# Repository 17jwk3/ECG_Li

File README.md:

# Real-time Wearable-based Cardiac Monitoring with Machine Learning
This project was part of ELEC490/498: Electrical Computer Engineering Capstone Project. A 3 semester long undertaking at Queen's Univeristy, Ontario, Canada. 

## Design Problem
Heart disease describes a range of conditions that affect a person’s heart, including blood vessel disease, arrhythmias, valve disease, etc.Various tests are used to diagnose heart conditions. Doctors start with a risk assessment looking into medical history, blood pressure, as well as past and current symptoms but further tests may be required. These methods can be hard to access for most people, due to socio-economic factors. This is a long and outdated process in the digital era of telemedicine. Doctors and patients need fast, easily accessible procedures. 

Many forms of it can be prevented with healthy lifestyle choices and medical interventions. Stress can affect the body mentally and physically left unchecked manifests as an increased heart rate among other symptoms contributing to high blood pressure, diabetes, and heart disease.

Computational advancements have increased the ability to concurrently predict and prevent cardiac abnormalities. Thus creating faster, less intrusive, and more easily accessible methods for patients and practitioners alike.

## Design and Implementaiton

Low-cost ECG (electrocardiogram) electrodes using a 3 lead configuraiton are used to capture impulses through the heart muscles and transmit the information via Bluetooth to a machine-learning algorithm in real-time to provide actionable feedback on potential abnormalities and stress levels via a Graphical User Interface, as seen in the following implementation pipeline.

---------------

### Hardware @17jwk3

The PCB uses a ESP32-C3-MINI-1-N4, a Li-Po with a battery charging module and a buck conmverter to supply 3.3V to the rest of the components. 
The main ECG components are an AD8232 opAmp board utilized for reading the electrical signals of the wearers heart and jack port for the 3 leads. 

#### PCB
This is a 4 layer PCB board that uses a AD8232 breakout board for the ECG pickup. 
The schematic, featuring over charge and discharge protection, switches to control: MCU power, 5V (charging) and Battery power. Also includes ESD protection for usb type C. The brains is an ESP32-C3-MINI-1-N4.

#### PCB layout 

#### Schematic

#### Findings & Changes

The selected ESP32 module was a "standard" component for JLCPCB which means it costed much more to manufacture this board then originally anticipated. A chip that does not require "standard" assembly would be selected going forward. 

With more time, the AD8232 module would be integrated onto the board to increase portability with a very small lipo battery. Additional changes would be made to optimize the layout, add more LEDs for feedback etc. 

The output of the AD8232 may have needed to include a pulldown resistor. 

---------------

### Data Acquisition @17jwk3
#### Design
Data is acquired using the AD8323 amplifier and processed by the ESP32 microcontroller. The amplifier is connected to a 3-lead system placed on the end-user’s person. The top L and R leads are used for data acquisition, while the third and lower lead is the grounding lead.  

The data is sampled at 6 seconds with a 115,200 baud rate. It uses a fixed 360 frequency in accordance with the arrhythmia dataset. Heart beats are characterized by shape and frequency. Abnormalities distinguished by pace (Sinus Arrhythmia, Bradycardia, etc.) would incur informational loss or distortion from domain resampling .

The firmware was coded using the Arduino IDE, a variant of the C++ programming language. It records when both L and R leads sense an electrical signal, as to avoid null readings from not being applied.

In order to create the dataset locally, run 'Models and Prediction/reciever.py'.

#### Findings & Changes

Modification in limb electrode placement invokes changes in ECG wave amplitudes, which may alter the clinical limits of ECG normality detection. It was uncovered that leads placed no further than 12” apart yield the cleanest readings. 

---------------

### Processing and Filtering @CTy27
#### Design
Processing was designed to address missing values and noise artifacts from the raw ECG data using the appropriate filtering methods.

The constraints surrounding hardware filters far outweighed those using software, as hardware filters are more expensive, more difficult to test, and would increase the PCB footprint. Software filtering allows for greater control and optimization which leads to a more optimally processed resulting signal.

A technique known as imputation was used to recover lost values by synthesizing datapoints that hardware failed to capture. Particularly, K-Nearest Neighbors (KNN) imputation is a method used to impute missing values by finding the K closest observations and using their respective values to ‘fill in’ the missing ones. In the application of ECG processing, this method of imputation is beneficial as it accounts for the temporal structure of the data, making KNN imputation a natural choice.

The chosen implementation uses a 3rd order, lowpass Butterworth filter with a cutoff frequency of 50 Hz. 50Hz was found to be the optimal amount as observable high-frequency artifacts from power line interference and EMG were removed without limiting the low-frequency salient information. Lowering this cut-off frequency further resulted in distortion to the amplitude of the peaks, which would have adversely affected the prediction model’s performance. 

#### Findings & Changes
Testing different filters and parameters was largely trial and error testing. Lowpass, high pass, bandpass, and notch filters were all tested, adjusting cut-off frequencies and passbands as appropriate. 

High pass and bandpass filters were susceptible to baseline wander, from samples 4,000 – 5,000 that the signal baseline drifts upwards. The high pass was also unable to filter out the high-frequency noise induced by Electromyography muscular activity (EMG), motion artifacts, and residual channel noise. The clear choice was lowpass as it maintains the salient, low-frequency information without distorting the signal with baseline wander. 

There lies uncertainty in the exclusive use of lowpass to filter out noise, as a bandpass and a notch filter ensemble are standard for ECG data.  Solely relying on low-pass filters is not a common approach, however, the final product was sufficient for the classification models to perform adequately. 

---------------

### Arrhythmia Detection @alexkoch14
#### Design
The arrhythmia model was trained on the MIT-BIH database, containing 48-half-hour excerpts of two-channel ambulatory ECG recordings, obtained from 47 subjects studied by the BIH arrhythmia laboratory between 1975 and 1979.

The recordings were digitized at 360 samples per second and two or more cardiologists independently annotated each record.

The recordings were extracted using wfdb, the Python wave-form database package. ECG signals are transformed into snippets during the data pre-processing step as the model analyzes one-dimensional input data. 

Heartbeats in the first or last 3 seconds of the half-hour recording are ignored to reduce data clipping sizes, as is for any non-beat annotations. Beat symbols are encoded as abnormal (1) or normal (0). 

A sliding window of 6 seconds per beat segment is used to capture the current beat and those adjacent to retain enough information from encompassed patterns ensuring a 2-3 beat overlap. 
The following graph demonstrates that encoded abnormal beats (those other than ‘N’, later encoded to 1) yield an even distribution, thus eliminating the need for resampling. 

Heartbeat voltages range among individuals depending on anatomy, body composition, blood volume, and ECG lead placement. Z-score normalization standardizes values into how much each reading deviates from the mean of all readings within the sample window.

In order to create the dataset locally, run 'Models and Prediction/arrhythmia_data.py'.

Leave-One-Out Crass-validation was employed via a hold-out set. The database was divided into three sets using a 60/30/10 train/validation/test split.
The holdout set primarily sought to encompass ~5 unseen subjects, consequentially representing ~10% of the data. 

The Deep-Learning (DL) model follows a Convolutional Neural Network architecture (CNN) using a TensorFlow backend.

arr_model_v4 uses a shallow, wide and simple architecture to overcome common real-time classification issues. 

The dataset has few features, but lots of records. This is perfect for DL models that need fewer parameters and sample complexity to achieve acceptable performance.

The model was trained on three passings of the training data (epochs). Accuracy decreased, loss increased, and overfitting began to occur beyond this point. 

In order to replicate the model, run 'Models and Prediction/arrhythmia_model.py'.

#### Findings & Changes
arr_model_v4’s performance indicates 87.7% accuracy and 84% recall on the test set, which comprises unseen patients, as seen in 'media/CNN_v4_results.txt'.

This is satisfactory for real-time classification uses which aren’t meant to serve as a clinical diagnosis. 

It showed minimal signs of overfitting with training loss and validation losses of 0.2195 and 0.2264 respectively. 

A limitation of the current methodology lies in grouping all abnormal patterns to obtain even distribution without resampling. It is possible that CNN v4’s ~90% accuracy is accredited is predicting 80% of abnormality types with 100% accuracy, and the remaining 20% with 0% accuracy. The model might not be able to predict less prevalent abnormality patterns while being excellent in predicting common ones.

---------------

### Stress Detection @alexkoch14
#### Design
The multimodal SWELL Knowledge Work dataset for stress modeling (SWELL-KW) contains data from 25 participants (~3 hours each) performing typical office work (writing reports, reading emails, etc.) under 3 conditions: no stress (0), email interruptions (1) and time pressure (2).

The stress model was trained on HRV metrics obtained from the SWELL-KW dataset.
Inter-beat interval (IBI) samples are extracted from the raw ECG signal of each subject over the 3-hour time series. 
HRV indices are then computed on a subset of the IBI signal array. New samples are appended to the IBI array while the oldest is removed from the beginning,creating a sliding window of HRV indices over a fixed acquisition window analogous to the arrhythmia data. 
This facilitates a granular study of how momentary heartbeat patterns and concurrent HRV metrics reflect a subject’s stress level. 

HRV metrics are computed from the input filtered signal using hrv-analysis Python library.

Leave-One-Out Crass-validation was employed via a hold-out set. The database was divided into three sets using a 60/30/10 train/validation/test split.
The holdout set primarily sought to encompass ~3 unseen subjects, consequentially representing ~10% of the data. 

Twenty-three classification models were then assessed using the LazyPredict Python library, indicating Guassian Naive Bayes provides the best time/accuracy trade-off.

In order to replicate the model, run 'Models and Prediction/stress_model.py'.

#### Findings & Changes

Stress model performance indicates a 57.1% F1-score on the validaiton set and 67.6% F1-Score on the test set, as seen in media/stress_model_v5_results.txt

The disparity in validation and testing sets accentuates some underlying points of issue. 

Models possess inherent predictive error which may lead to a relatively higher score on the test set due to chance.

The current neurobiological evidence suggests that HRV is impacted by stress and supports its use for an objective assessment of health, but it can be expressed through other psychological pathways (EDA, body posture, etc.).
These added features, which are not part of the feature set, are perhaps expressed more vividly in the validation subjects. 
Equivalently said, fewer people in the validation set tend to manifest stress predominantly through HRV than other physiological pathways. This is a limitation of training the stress model on a subset of a subset of the SWELL-KW dataset. 

Nonetheless, results are satisfactory for obtaining real-time assessments. Stress mitigation is a preventative step in cardiac abnormality evasion. It is the first line of defense, but an overpassed subject will get caught using CNN v4 used in arrhythmia detection.  

---------------

### Graphical User Interface @CTy27
#### Design
The GUI was designed to be responsive, have a low learning curve, and supply key metrics such as heart rate, abnormality likelihood, presence of stress, and supplement heart rate variability (HRV) metrics such as mean RR. These metrics were selected after conducting extensive research into clinical grade industry standard ECG monitors, to replicate their functionality.

The Python Tkinter library was selected to allow for seamless integration with the constituent sub-systems, as it can function using a single script requiring the end user to only use one file to access the functionality. Moreover, Tkinter is open sourced which ensures compatibility and facilitates future development. 

User testing was performed by gathering feedback from preliminary UI drafts. Users appreciated the color-coded feedback and unified design language, but feedback ultimately indicated that the lighter color scheme made the GUI appear less intimidating. 

The final design uses a clean modern interface with clear visualizations. It includes added features such as the ability to save and export data for further analysis via PDF using the “See Full Report” button. 

#### Findings & Changes
The GUI acts as a proof of concept and does not store any medical data; it loses all information once the front end is closed and thus is not bound to any regulatory compliance. The information displayed is not a formal diagnosis and the documentation serves as a clear indicator of whether a medical professional should be consulted. 

It performs similarly to commercial products, allowing for user initiation of ECG readings, and those readings being displayed visually once complete. 

The largest weakness lies in the usage of Python. The Tkinter library is very limiting from a design perspective, making it difficult to implement a modern-looking dashboard. 
It only supports certain shapes, images, and colors which makes the overall appearance less customizable. 
Another weakness lies in the Tkinter structure which required all other sub-systems’ code to be embedded into a single file due. Restarting the entire program is therefore necessary to initiate a new run. 
This is inconvenient to the end user as this operation is computationally expensive and can add time to the entire experience. Using another Python library like PyQt, or a mobile app software like Swift would likely increase the overall user experience and allow for multiple runs without restarting the entire front end, but further research would need to be conducted. 

---------------

## Replication 

Clone the repositiry to you local machine and run:
'ECG_Li\Models and Prediction\gui.py'

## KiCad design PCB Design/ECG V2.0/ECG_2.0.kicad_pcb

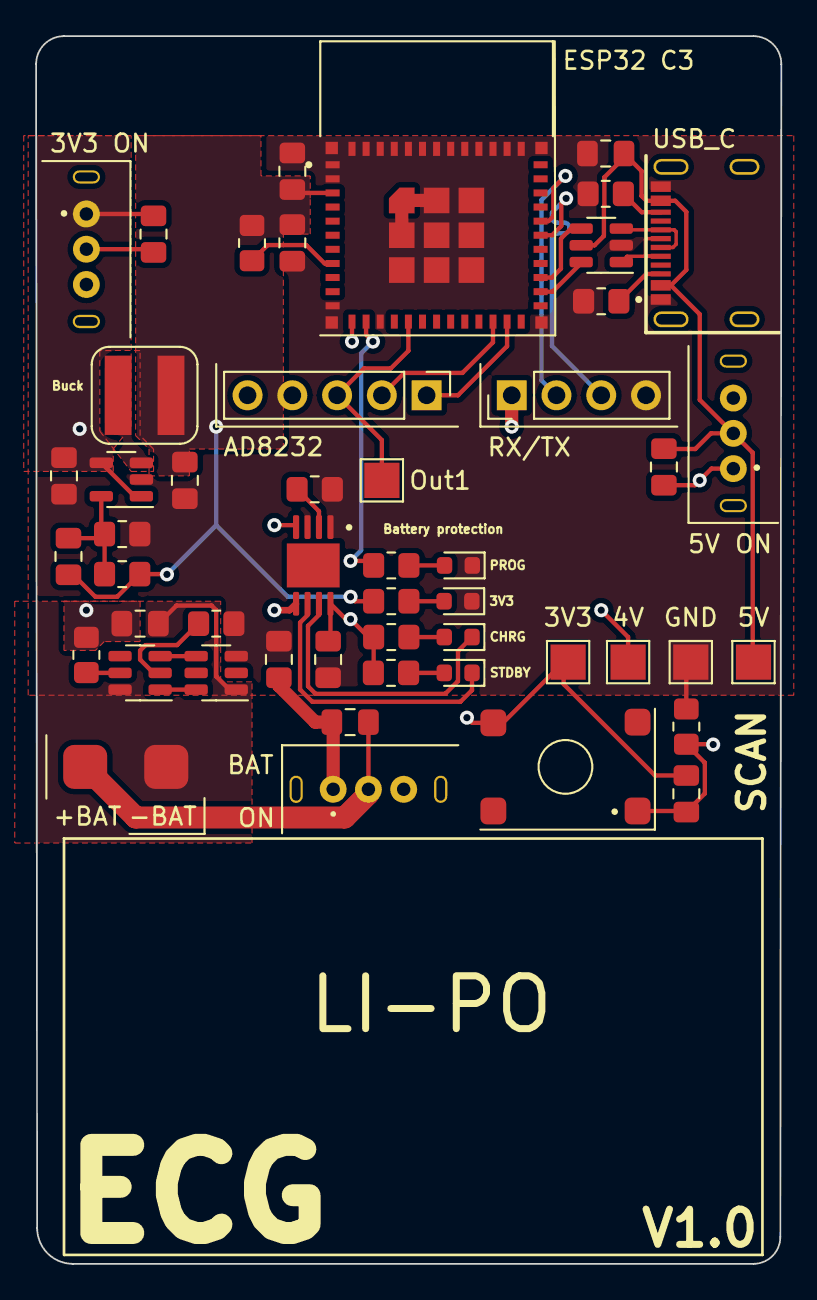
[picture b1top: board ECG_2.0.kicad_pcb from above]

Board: 4 copper layers, 42.3 x 69.7 mm, 50 parts (0 on the bottom side), 35 nets.

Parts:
3V3: TP 3V3; TestPoint_Pad_2.0x2.0mm
4V: TP 4V; TestPoint_Pad_2.0x2.0mm
5V: TP 5V; TestPoint_Pad_2.0x2.0mm
C1, C4, C5, C10, C12, C13: 100nF; C_0805_2012Metric_Pad1.18x1.45mm_HandSolder
C2, C3, C8, C9, C11: 10uF; C_0805_2012Metric_Pad1.18x1.45mm_HandSolder
C6: 4.7uF; C_0805_2012Metric_Pad1.18x1.45mm_HandSolder
C7: 10pF; C_0805_2012Metric_Pad1.18x1.45mm_HandSolder
D1: RED; LED_0603_1608Metric
D2: Green LED; LED_0603_1608Metric
D3: Blue LED; LED_0603_1608Metric
D4: LED; LED_0603_1608Metric
GND: TP GND; TestPoint_Pad_2.0x2.0mm
J1: 01x05_Female; PinHeader_1x05_P2.54mm_Vertical
J2: JST_01x04_Male; PinHeader_1x04_P2.54mm_Vertical
L1: 2.2uH; CY43-2.2uH
Out1: TP Output; TestPoint_Pad_2.0x2.0mm
R1, R6, R8: 10K; R_0805_2012Metric_Pad1.20x1.40mm_HandSolder
R2, R3, R12: 1K; R_0805_2012Metric_Pad1.20x1.40mm_HandSolder
R4, R7: 220; R_0805_2012Metric_Pad1.20x1.40mm_HandSolder
R5: 45K; R_0805_2012Metric_Pad1.20x1.40mm_HandSolder
R9, R10: 5K1; R_0805_2012Metric_Pad1.20x1.40mm_HandSolder
R11: 100R; R_0805_2012Metric_Pad1.20x1.40mm_HandSolder
Rprog1: 1k4; R_0805_2012Metric_Pad1.20x1.40mm_HandSolder
U1: Li-Po; Battery Solder Pad 2.5x2.0mm
U2: TP4056-C21417; MSOP-8-1EP_3x3mm_P0.65mm_EP2.5x3mm_Mask1.73x2.36mm
U3: USBLC6-2SC6; SOT-23-6
U4: Battery_Switch; Battery_swt
U5: 5V_switch; 5V
U6: TLV62568DBV; SOT-23-5
U7: MCU_switch; 3V3 SWT
U8: Tactile_push_button_6x6mm; Tactile_pushbutton_6x6mm
U9: USB-TYPE0-C-16P; HRO_TYPE-C-31-M-12
U10: ESP32-C3-MINI-1-N4; XCVR_ESP32-C3-MINI-1-N4
U11: FS8205A; SOT-23-6
U12: DW01; SOT-23-6

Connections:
+3V3: 3V3.1, C1.1, C7.1, C8.1, C9.1, C10.1, J1.4, J2.1, L1.2, R5.1, R7.1, R8.1, U8.4, U10.3 (3V3)
+4V: 4V.1, C6.1, C13.1, U6.1 (EN), U6.4 (VIN), U7.1
+5V: C3.1, C12.1, R2.2, R3.2, U2.4 (VCC), U2.8 (CE), U5.1
+BATT: C2.1, C4.1, C5.1, C13.2, R11.2, U2.5 (BAT), U4.1, U7.2
+LO: J1.1, U10.23 (IO9)
-LO: J1.2, U10.22 (IO8)
/RX: J2.3, U10.30 (RXD0)
/TX: J2.2, U10.31 (TXD0)
BTN: C1.2, R1.1, U8.1, U10.12 (IO0)
BatO: C5.2, U1.1 (+Bat), U4.2
DN: U3.1 (I/O1), U9.A7 (DN1), U9.B7 (DN2)
DNO: U3.6 (I/O1), U10.26 (IO18)
DP: U3.3 (I/O2), U9.A6 (DP1), U9.B6 (DP2)
DPO: U3.4 (I/O2), U10.27 (IO19)
GND: C2.2, C3.2, C6.2, C8.2, C9.2, C10.2, C11.2, D3.1 (K), D4.1 (K), GND.1, J1.5, J2.4, R1.2, R6.2, R9.2, R10.2, R12.1, Rprog1.2, U2.1 (TEMP), U2.3 (GND), U3.2 (GND), U6.2 (GND), U9.A1_B12 (GND), U9.B1_A12 (GND), U10.1 (GND), U10.2 (GND), U10.11 (GND), U10.14 (GND), U10.36 (GND), U10.37 (GND), U10.38 (GND), U10.39 (GND), U10.40 (GND), U10.41 (GND), U10.42 (GND), U10.43 (GND), U10.44 (GND), U10.45 (GND), U10.46 (GND), U10.47 (GND), U10.48 (GND), U10.49 (EPAD), U10.50 (GND), U10.51 (GND), U10.52 (GND), U10.53 (GND), U11.3 (S2)
In_5V: 5V.1, C11.1, C12.2, U3.5 (VBUS), U5.2, U9.A4_B9 (VBUS), U9.B4_A9 (VBUS)
LED: R4.1, U10.13 (IO1)
unnamed: D1.2 (A), R2.1
unnamed: D1.1 (K), U2.7 (CHRG)
unnamed: D2.2 (A), R3.1
unnamed: D2.1 (K), U2.6 (STDBY)
unnamed: D3.2 (A), R4.2
unnamed: D4.2 (A), R7.2
unnamed: Rprog1.1, U2.2 (PROG)
unnamed: C7.2, R5.2, R6.1, U6.5 (FB)
unnamed: L1.1, U6.3 (SW)
unnamed: R9.1, U9.B8 (CC1)
unnamed: R10.1, U9.B5 (CC2)
unnamed: R8.2, U10.8 (EN)
unnamed: U11.6 (G1), U12.1 (OD)
unnamed: U11.4 (G2), U12.3 (OC)
unnamed: R11.1, U12.5 (VCC)
unnamed: R12.2, U12.2 (VM)
Output: J1.3, Out1.1, U10.16 (IO10)
VSS: C4.2, U1.2 (-Bat), U11.1 (S1), U12.6 (GND)

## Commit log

2023-01-26 Initial setup
    to new beginnings, your welcome.
2023-01-26 Continued work
    added buck converter and switch footprint
2023-01-27 Updates to schematic
    Correct and added MCU
2023-01-27 added sources files
2023-02-02 changes to pcb, added ad8232
2023-02-02 Create Prediction
2023-02-02 Prediction Models
2023-02-05 Added user samples and receiver file
2023-02-06 updating ECG placement test results
2023-02-06 update notes
2023-02-07 changes to schematic of pcb
2023-02-10 Performance results
    Performance results of arr and stress models.
2023-02-10 Directory clean-up
2023-02-10 schem done, pcb 50%
2023-02-12 adding loss / acc curves
2023-02-14 second last iteration hopefully
    pcb design, pending Bruno approval
2023-02-14 added figures
2023-02-26 Final PCB changes
2023-02-26 Deleted old corrupt files
2023-02-26 readMe and media updates
2023-02-26 BOM edits
2023-02-27 Gerber files and Larger pcb due to manufacturing limits
2023-02-28 Final pcb
2023-02-28 media changes
2023-02-28 small updates to pcb
2023-03-02 added li-po and esp32 to models
2023-03-05 New CNN model
2023-03-06 Implemented a new stress prediction model
2023-03-14 Improved PCB design and Improved renderings
2023-03-17 connections issue on pcb deisgn
2023-03-22 Final GUI implementaiton
2023-03-23 Showcase code changes
2023-04-04 updated Schematic to reflect hardware testing issues
    Changed schematic for USB-C, had the pin our wrong.
    Changed through hole switch components and USB-C through hole for better fit.
2023-04-04 small backup changes
2023-04-17 Cleaning up the directories
2023-04-17 read me
